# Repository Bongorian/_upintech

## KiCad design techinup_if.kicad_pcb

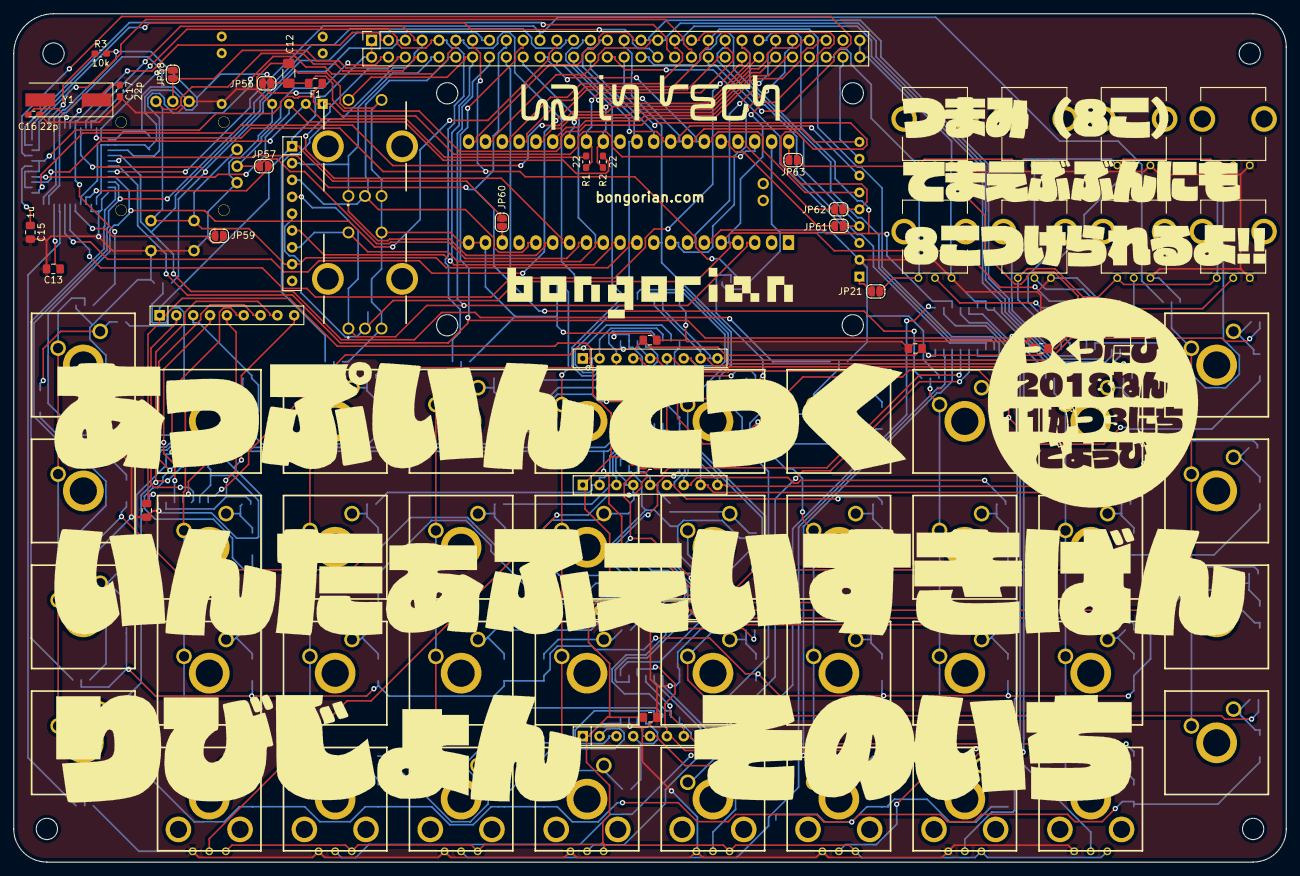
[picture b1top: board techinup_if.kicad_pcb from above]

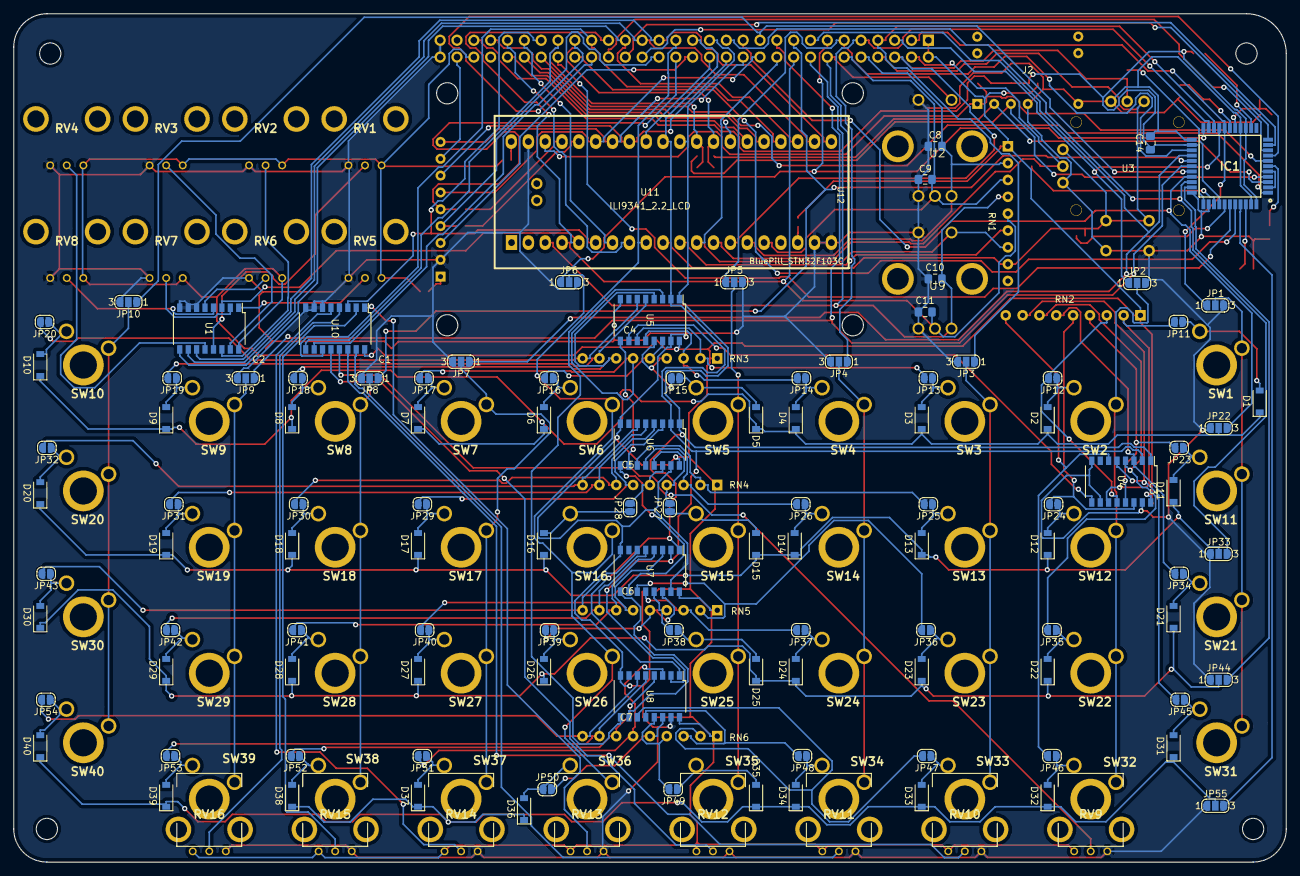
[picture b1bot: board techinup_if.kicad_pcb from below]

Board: 2 copper layers, 192.0 x 128.0 mm, 206 parts (117 on the bottom side), 187 nets.

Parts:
C1, C2, C3, C4, C5, C6, C7, C13, C14: 0.1u; C_0805_2012Metric_Pad1.15x1.40mm_HandSolder
C8, C9, C10, C11: C; C_0805_2012Metric_Pad1.15x1.40mm_HandSolder
C12: 10u; C_1206_3216Metric_Pad1.42x1.75mm_HandSolder
C15: 1u; C_0805_2012Metric_Pad1.15x1.40mm_HandSolder
C16, C17: 22p; C_0603_1608Metric_Pad1.05x0.95mm_HandSolder
D1, D2, D3, D4, D5, D6, D7, D8, D9, D10, D11, D12, D13, D14, D15, D16, D17, D18, D19, D20, D21, D22, D23, D24, D25, D26, D27, D28, D29, D30, D31, D32, D33, D34, D35, D36, D37, D38, D39, D40: D; D_SOD-123
F1: Fuse_Small; C_0805_2012Metric_Pad1.15x1.40mm_HandSolder
IC1: ATMEGA32U4-AU; QFP80P1200X1200X120-44N
J2: Conn_01x05_Male; USBC
J3: Conn_02x30_Odd_Even; PinSocket_2x30_P2.54mm_Vertical
JP1, JP2, JP3, JP4, JP5, JP6, JP7, JP8, JP9, JP10, JP22, JP33, JP44, JP55: SolderJumper_3_Open; SolderJumper-3_P1.3mm_Open_RoundedPad1.0x1.5mm_NumberLabels
JP11, JP12, JP13, JP14, JP15, JP16, JP17, JP18, JP19, JP20, JP21, JP23, JP24, JP25, JP26, JP27, JP28, JP29, JP30, JP31, JP32, JP34, JP35, JP36, JP37, JP38, JP39, JP40, JP41, JP42, JP43, JP45, JP46, JP47, JP48, JP49, JP50, JP51, JP52, JP53, JP54, JP56, JP60, JP63: Jumper_NO_Small; SolderJumper-2_P1.3mm_Open_RoundedPad1.0x1.5mm
JP57: JOYX; SolderJumper-2_P1.3mm_Open_RoundedPad1.0x1.5mm
JP58: JOYY; SolderJumper-2_P1.3mm_Open_RoundedPad1.0x1.5mm
JP59: JOYSW; SolderJumper-2_P1.3mm_Open_RoundedPad1.0x1.5mm
JP61, JP62: LCD32; SolderJumper-2_P1.3mm_Open_RoundedPad1.0x1.5mm
R1, R2: 22; R_0603_1608Metric_Pad1.05x0.95mm_HandSolder
R3: 10k; R_0603_1608Metric_Pad1.05x0.95mm_HandSolder
RN1, RN2, RN3, RN4, RN5, RN6: R_Network08; R_Array_SIP9
RV1, RV2, RV3, RV4, RV5, RV6, RV7, RV8: R_POT; RV09AF4030KB10K
RV9, RV10, RV11, RV12, RV13, RV14, RV15, RV16: R_POT; RV09_horizonal
SW1, SW2, SW3, SW4, SW5, SW6, SW7, SW8, SW9, SW10, SW11, SW12, SW13, SW14, SW15, SW16, SW17, SW18, SW19, SW20, SW21, SW22, SW23, SW24, SW25, SW26, SW27, SW28, SW29, SW30, SW31, SW32, SW33, SW34, SW35, SW36, SW37, SW38, SW39, SW40: SW_Push; cherry
U1, U10: 4051; SOP-16_4.4x10.4mm_P1.27mm
U2, U9: PEC12R-4225F-S0024; PEC12R-4XXXF-SXXXX_1
U3: joystick
U4, U5, U6, U7, U8: 74LS165; SOP-16_4.4x10.4mm_P1.27mm
U11: ILI9341_2.2_LCD; ILI9341_2.2
U12: BluePill_STM32F103C
Y1: Crystal_Small; Crystal_SMD_HC49-SD
x1, x2, x3, x4: MountingHole_3.2mm_M3

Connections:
4051_OUT_1: J3.39, U1.3, U12.5
4051_OUT_2: J3.47, U10.3, U12.6
4051_S1_1: J3.33, U1.11, U12.21
4051_S1_2: J3.41, U10.11, U12.24
4051_S2_1: J3.35, U1.10, U12.22
4051_S2_2: J3.43, R1.2, U10.10, U12.28
4051_S3_1: J3.37, U1.9, U12.23
4051_S3_2: J3.45, R2.2, U10.9, U12.29
74165_CE: C1.2, C2.2, C3.1, C4.1, C5.1, C6.1, C7.1, C8.2, C9.2, C10.2, C11.2, C12.2, C13.2, C14.2, C15.2, C16.2, C17.2, IC1.15, IC1.23, IC1.33, IC1.35, IC1.43, J2.4, J2.5, J3.59, J3.60, JP1.3, JP2.3, JP3.3, JP4.3, JP5.3, JP6.3, JP7.3, JP8.3, JP9.3, JP10.3, JP22.1, JP33.1, JP44.1, JP55.1, RV1.3, RV2.3, RV3.3, RV4.3, RV5.3, RV6.3, RV7.3, RV8.3, RV9.3, RV10.3, RV11.3, RV12.3, RV13.3, RV14.3, RV15.3, RV16.3, U1.6, U1.7, U1.8, U2.2, U2.5, U3.3, U3.6, U3.9, U3.10, U4.8, U4.10, U4.15, U5.8, U5.15, U6.8, U6.15, U7.8, U7.15, U8.8, U8.15, U9.2, U9.5, U10.6, U10.7, U10.8, U11.2, U12.19, U12.20, U12.39
74165_CK: J3.29, U4.2, U5.2, U6.2, U7.2, U8.2, U12.31
74165_OUT: J3.31, U8.9, U12.9
74165_SH: J3.27, U4.1, U5.1, U6.1, U7.1, U8.1, U12.30
CS_LCD: J3.30, U11.3
CS_STM: J3.28, U12.32
D7: IC1.1, J3.48
D+: IC1.4, J2.3, R2.1
D-: IC1.3, J2.2, R1.1
D_C: J3.32, JP62.1, U11.5
IO_A2: IC1.40, J3.44
IO_A3: IC1.39, J3.46
JOY_SW: J3.8, JP59.1, RN1.8, U3.1, U3.4, U3.7, U3.8, U12.10
JOY_X: J3.4, JP57.1, U3.5, U12.13
JOY_Y: J3.6, JP58.1, U3.2, U12.14
KEY1: JP11.2, RN2.2, U4.11
KEY2: JP12.2, RN2.3, U4.12
KEY3: JP23.2, RN2.4, U4.13
KEY4: JP24.2, RN2.5, U4.14
KEY5: JP34.2, RN2.6, U4.3
KEY6: JP35.2, RN2.7, U4.4
KEY7: JP45.2, RN2.8, U4.5
KEY8: JP46.2, RN2.9, U4.6
KEY9: JP13.2, RN3.2, U5.11
KEY10: JP14.2, RN3.3, U5.12
KEY11: JP15.2, RN3.4, U5.13
KEY12: JP16.2, RN3.5, U5.14
KEY13: JP17.2, RN3.6, U5.3
KEY14: JP18.2, RN3.7, U5.4
KEY15: JP19.2, RN3.8, U5.5
KEY16: JP20.2, RN3.9, U5.6
KEY17: JP25.2, RN4.2, U6.11
KEY18: JP26.2, RN4.3, U6.12
KEY19: JP27.2, RN4.4, U6.13
KEY20: JP28.2, RN4.5, U6.14
KEY21: JP29.2, RN4.6, U6.3
KEY22: JP30.2, RN4.7, U6.4
KEY23: JP31.2, RN4.8, U6.5
KEY24: JP32.2, RN4.9, U6.6
KEY25: JP36.2, RN5.2, U7.11
KEY26: JP37.2, RN5.3, U7.12
KEY27: JP38.2, RN5.4, U7.13
KEY28: JP39.2, RN5.5, U7.14
KEY29: JP40.2, RN5.6, U7.3
KEY30: JP41.2, RN5.7, U7.4
KEY31: JP42.2, RN5.8, U7.5
KEY32: JP43.2, RN5.9, U7.6
KEY33: JP47.2, RN6.2, U8.11
KEY34: JP48.2, RN6.3, U8.12
KEY35: JP49.2, RN6.4, U8.13
KEY36: JP50.2, RN6.5, U8.14
KEY37: JP51.2, RN6.6, U8.3
KEY38: JP52.2, RN6.7, U8.4
KEY39: JP53.2, RN6.8, U8.5
KEY40: JP54.2, RN6.9, U8.6
LCD_RESET: J3.34, JP61.1, U11.4
LED: J3.58, U11.8
MISO_3.3: J3.24, U11.9, U12.34
MISO_atmega: IC1.11, J3.36
MOSI_3.3: J3.22, U11.6, U12.35
MOSI_atmega: IC1.10, J3.38
unnamed: C13.1, IC1.42
unnamed: C15.1, IC1.6
unnamed: C16.1, IC1.16, Y1.2
unnamed: C17.1, IC1.17, Y1.1
unnamed: D1.1, D2.1, D3.1, D4.1, D5.1, D6.1, D7.1, D8.1, D9.1, D10.1, JP22.2
unnamed: D1.2, JP11.1, SW1.2
unnamed: D2.2, JP12.1, SW2.2
unnamed: D3.2, JP13.1, SW3.2
unnamed: D4.2, JP14.1, SW4.2
unnamed: D5.2, JP15.1, SW5.2
unnamed: D6.2, JP16.1, SW6.2
unnamed: D7.2, JP17.1, SW7.2
unnamed: D8.2, JP18.1, SW8.2
unnamed: D9.2, JP19.1, SW9.2
unnamed: D10.2, JP20.1, SW10.2
unnamed: D11.1, D12.1, D13.1, D14.1, D15.1, D16.1, D17.1, D18.1, D19.1, D20.1, JP33.2
unnamed: D11.2, JP23.1, SW11.2
unnamed: D12.2, JP24.1, SW12.2
unnamed: D13.2, JP25.1, SW13.2
unnamed: D14.2, JP26.1, SW14.2
unnamed: D15.2, JP27.1, SW15.2
unnamed: D16.2, JP28.1, SW16.2
unnamed: D17.2, JP29.1, SW17.2
unnamed: D18.2, JP30.1, SW18.2
unnamed: D19.2, JP31.1, SW19.2
unnamed: D20.2, JP32.1, SW20.2
unnamed: D21.1, D22.1, D23.1, D24.1, D25.1, D26.1, D27.1, D28.1, D29.1, D30.1, JP44.2
unnamed: D21.2, JP34.1, SW21.2
unnamed: D22.2, JP35.1, SW22.2
unnamed: D23.2, JP36.1, SW23.2
unnamed: D24.2, JP37.1, SW24.2
unnamed: D25.2, JP38.1, SW25.2
unnamed: D26.2, JP39.1, SW26.2
unnamed: D27.2, JP40.1, SW27.2
unnamed: D28.2, JP41.1, SW28.2
unnamed: D29.2, JP42.1, SW29.2
unnamed: D30.2, JP43.1, SW30.2
unnamed: D31.1, D32.1, D33.1, D34.1, D35.1, D36.1, D37.1, D38.1, D39.1, D40.1, JP55.2
unnamed: D31.2, JP45.1, SW31.2
unnamed: D32.2, JP46.1, SW32.2
unnamed: D33.2, JP47.1, SW33.2
unnamed: D34.2, JP48.1, SW34.2
unnamed: D35.2, JP49.1, SW35.2
unnamed: D36.2, JP50.1, SW36.2
unnamed: D37.2, JP51.1, SW37.2
unnamed: D38.2, JP52.1, SW38.2
unnamed: D39.2, JP53.1, SW39.2
unnamed: D40.2, JP54.1, SW40.2
unnamed: IC1.13, R3.1
unnamed: IC1.36, JP57.2
unnamed: IC1.37, JP58.2
unnamed: IC1.38, JP59.2
unnamed: JP1.2, SW1.1, SW11.1, SW21.1, SW31.1
unnamed: JP2.2, SW2.1, SW12.1, SW22.1, SW32.1
unnamed: JP3.2, SW3.1, SW13.1, SW23.1, SW33.1
unnamed: JP4.2, SW4.1, SW14.1, SW24.1, SW34.1
unnamed: JP5.2, SW5.1, SW15.1, SW25.1, SW35.1
unnamed: JP6.2, SW6.1, SW16.1, SW26.1, SW36.1
unnamed: JP7.2, SW7.1, SW17.1, SW27.1, SW37.1
unnamed: JP8.2, SW8.1, SW18.1, SW28.1, SW38.1
unnamed: JP9.2, SW9.1, SW19.1, SW29.1, SW39.1
unnamed: JP10.2, SW10.1, SW20.1, SW30.1, SW40.1
unnamed: JP21.2, U11.1
unnamed: JP60.1, U12.18
unnamed: JP61.2, U12.36
unnamed: JP62.2, U12.37
unnamed: JP63.2, U12.40
unnamed: RV1.2, U1.13
unnamed: RV2.2, U1.14
unnamed: RV3.2, U1.15
unnamed: RV4.2, U1.12
unnamed: RV5.2, U1.1
unnamed: RV6.2, U1.5
unnamed: RV7.2, U1.2
unnamed: RV8.2, U1.4
unnamed: RV9.2, U10.13
unnamed: RV10.2, U10.14
unnamed: RV11.2, U10.15
unnamed: RV12.2, U10.12
unnamed: RV13.2, U10.1
unnamed: RV14.2, U10.5
unnamed: RV15.2, U10.2
unnamed: RV16.2, U10.4
unnamed: U4.9, U5.10
unnamed: U5.9, U6.10
unnamed: U6.9, U7.10
unnamed: U7.9, U8.10
PA8: J3.53, U12.25
PB0: IC1.8, J3.42
PWR: C1.1, C2.1, C3.2, C4.2, C5.2, C6.2, C7.2, J3.1, J3.2, J3.56, JP21.1, JP56.2, JP60.2, JP63.1, RN1.1, RN2.1, RN3.1, RN4.1, RN5.1, RN6.1, RV1.1, RV2.1, RV3.1, RV4.1, RV5.1, RV6.1, RV7.1, RV8.1, RV9.1, RV10.1, RV11.1, RV12.1, RV13.1, RV14.1, RV15.1, RV16.1, U1.16, U4.16, U5.16, U6.16, U7.16, U8.16, U10.16
RE1_A: C8.1, J3.10, RN1.2, U2.1, U12.15
RE1_B: C9.1, J3.12, RN1.3, U2.3, U12.16
RE1_SW: J3.14, RN1.6, U2.4, U12.11
RE2_A: C10.1, J3.16, RN1.4, U9.1, U12.3
RE2_B: C11.1, J3.18, RN1.5, U9.3, U12.4
RE2_SW: J3.20, RN1.7, U9.4, U12.12
RX1: J3.50, U12.27
RX2: J3.51, U12.8
SCK_3.3: J3.26, U11.7, U12.33
SCK_atmega: IC1.9, J3.40
TX1: J3.52, U12.26
TX2: J3.49, U12.7
UVCC: F1.1, IC1.2, IC1.5, IC1.7, J2.1, U12.38
VCC: C12.1, C14.1, F1.2, IC1.14, IC1.24, IC1.34, IC1.44, J3.55, JP56.1, R3.2
col1: IC1.18, J3.3, JP1.1
col2: IC1.19, J3.5, JP2.1
col3: IC1.20, J3.7, JP3.1
col4: IC1.21, J3.9, JP4.1
col5: IC1.25, J3.11, JP5.1
col6: IC1.22, J3.13, JP6.1
col7: IC1.26, J3.15, JP7.1
col8: IC1.27, J3.17, JP8.1
col9: IC1.28, J3.19, JP9.1
col10: IC1.29, J3.21, JP10.1
row1: IC1.30, J3.23, JP22.3
row2: IC1.31, J3.25, JP33.3
row3: IC1.32, JP44.3
row4: IC1.41, JP55.3

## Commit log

2018-11-06 init
